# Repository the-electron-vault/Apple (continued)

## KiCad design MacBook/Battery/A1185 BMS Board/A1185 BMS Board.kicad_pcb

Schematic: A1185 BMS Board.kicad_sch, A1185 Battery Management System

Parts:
C1, C7, C13, C37: 100nF; MLCC-0603; Voltage 50V; Tolerance 10%; Manufacturer Part Number CL10B104KB8NNWC
C2, C3, C4, C8, C9, C14, C15, C19, C22, C28, C35: 100nF; MLCC-0402; Voltage 16V; Tolerance 10%; Manufacturer Part Number GCM155R71C104KA55J
C5: 4.7uF; MLCC-0805; Voltage 16V; Tolerance 10%; Manufacturer Part Number GRM21BR71C475KE51K
C6, C10, C21, C25, C33, C34: 1uF; MLCC-0805; Voltage 25V; Tolerance 10%; Manufacturer Part Number CL21B105KAFNNNE
C11, C12, C16, C17, C30, C32: 470nF; MLCC-0402; Voltage 10V; Tolerance 10%; Manufacturer Part Number KAM05AR71A474KH
C18, C27: 68pF; MLCC-0402; Voltage 50V; Tolerance 5%; Manufacturer Part Number CL05C680JB5NNNC
C20, C23, C24: 100nF; MLCC-0402; Voltage 16V; Tolerance 10%; Manufacturer Part Number GCM155R71C104KA55J; not fitted
C26: 150pF; MLCC-0402; Voltage 50V; Tolerance 5%; Manufacturer Part Number CL05C151JB5NNNC
C29: 47nF; MLCC-0603; Voltage 50V; Tolerance 10%; Manufacturer Part Number CL10B473KB8NNNC
C31: 2.2nF; MLCC-0402; Voltage 50V; Tolerance 10%; Manufacturer Part Number GRM155R71H222KA01D
C36: 1uF; MLCC-0805; Voltage 25V; Tolerance 10%; Manufacturer Part Number CL21B105KAFNNNE; not fitted
D1, D4, D5: 1SS355VMTE-17; SOD-323F; Voltage 90V; Manufacturer Part Number 1SS355VMTE-17
D2: RB751V-40TE-17; SOD-323F; Voltage 30V; Manufacturer Part Number RB751V-40TE-17
D3: UDZVTE-1733B; SOD-323F; Voltage 33V; Manufacturer Part Number UDZVTE-1733B
D6: UDZVTE-1718B; SOD-323F; Voltage 18V; Manufacturer Part Number UDZVTE-1718B
D7: MMBZ5V6ALT1G; SOT-23; Voltage 5.6V; Manufacturer Part Number MMBZ5V6ALT1G
F1: 12A; D6X; Voltage 32V; Manufacturer Part Number D6X
J1: BATT-TERM-POS; Manufacturer Part Number BATT-TERM-POS
J2, J3: CONN-1x1-0.6MM-TH; TH-0.6MM-1x1; Manufacturer Part Number CONN-1x1-0.6MM-TH
J4: BATT-TERM-NEG; Manufacturer Part Number BATT-TERM-NEG
J5: A1185 BLADE RCPT; A1185-BLADE-RECEPTACLE; Manufacturer Part Number A1185 BLADE RCPT
JP1: JUMPER-NO
LD1, LD2, LD3, LD4, LD5: HSMG-C110; HSMx-C110; Voltage 2.2V; Manufacturer Part Number HSMG-C110
Q1: AO3406; SOT-23; Voltage 30V; Manufacturer Part Number AO3406
Q2, Q3: TPC8107; SOIC-8; Voltage 30V; Manufacturer Part Number TPC8107
Q4, Q6: MMBT3906LT1G; SOT-23; Voltage 40V; Manufacturer Part Number MMBT3906LT1G
Q5, Q7, Q8, Q9, Q10: 2N7002K-T1-GE3; SOT-23; Voltage 60V; Manufacturer Part Number 2N7002K-T1-GE3
R1, R2, R3, R4, R14, R24, R28, R31, R32: 100; RES-0603; Tolerance 1%; Manufacturer Part Number RCA0603100RFKEA
R5, R11, R21, R36: 10; RES-0603; Tolerance 1%; Manufacturer Part Number RCA060310R0FKEA
R6, R7, R8, R34: 1k; RES-0402; Tolerance 1%; Manufacturer Part Number CRCW04021K00FKED
R9: 100k; RES-0603; Tolerance 1%; Manufacturer Part Number RCA0603100KFKEA
R10, R18, R35, R37: 100k; RES-0402; Tolerance 1%; Manufacturer Part Number CRCW0402100KFKED
R12, R19: 8.45k; RES-0402; Tolerance 1%; Manufacturer Part Number CRCW04028K45FKED
R13, R20, R33: 61.9k; RES-0402; Tolerance 1%; Manufacturer Part Number CRCW040261K9FKED
R15, R22, R23: 220k; RES-0402; Tolerance 1%; Manufacturer Part Number CRCW0402220KFKED
R16: 100; RES-0402; Tolerance 1%; Manufacturer Part Number CRCW0402100RFKED
R17: 100k; RES-0402; Tolerance 1%; Manufacturer Part Number CRCW0402100KFKED; not fitted
R25, R30, R38, R39, R40, R41, R43, R44, R45: 1M; RES-0402; Tolerance 1%; Manufacturer Part Number CRCW04021M00FKED
R26: 5m; RES-2512; Tolerance 1%; Manufacturer Part Number RLM25FEER005
R27, R29: 5.1k; RES-0402; Tolerance 1%; Manufacturer Part Number CRCW04025K10FKED
R42: 15k; RES-0402; Tolerance 1%; Manufacturer Part Number CRCW040215K0FKED
R46, R47: 100; RES-0805; Tolerance 1%; Manufacturer Part Number CRCW0805100RFKEA
R48: 130; RES-0402; Tolerance 1%; Manufacturer Part Number CRCW0402130RFKED
R49: 10k; RES-0402; Tolerance 1%; Manufacturer Part Number CRCW040210K0FKED
RT1, RT2: CONN-1x2-2MM-SMT; SMT-2MM-1x2; Manufacturer Part Number CONN-1x2-2MM-SMT
S1: APTCLGTV; Manufacturer Part Number APTCLGTV
TP1, TP2, TP3, TP4, TP5, TP6, TP7, TP8, TP9, TP10, TP11, TP12, TP13, TP14, TP15, TP16, TP17, TP18, TP19, TP20, TP21, TP22, TP23, TP24, TP25, TP26, TP27, TP28, TP29, TP30, TP31, TP32, TP33, TP34, TP35, TP36, TP37, TP38, TP39, TP40, TP41, TP42, TP43, TP44, TP45, TP46, TP47, TP48, TP49, TP50, TP51: TP; TP-SMT
U1: BQ29312ARTHR; VQFN-24-0.5-CH; Manufacturer Part Number BQ29312ARTHR
U2: BQ29401PW; TSSOP-8; Manufacturer Part Number BQ29401PW
U3: BQ20Z80DBT; TSSOP-38-0.5; Manufacturer Part Number BQ20Z80DBT

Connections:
/AFE_BAT: C6.1, D1.K, TP8.1, U1.22 (BAT)
/AFE_BAT_R: D1.A, R5.2
/AFE_CELL: R16.1, U1.8 (CELL)
/AFE_CHG: R29.2, U1.17 (CHG)
/AFE_DSG: R27.2, U1.23 (DSG)
/AFE_PACK: C10.1, D2.K, D3.K, TP13.1, U1.19 (PACK)
/AFE_PACK_R: D2.A, R11.2
/AFE_PMS: R9.2, TP12.1, U1.20 (PMS)
/AFE_SLEEP: R10.1, U1.16 (SLEEP)
/AFE_TOUT: R12.1, R19.1, TP17.1, U1.14 (TOUT)
/AFE_VC1_2: C1.1, R1.2, TP4.1, U1.1 (VC2), U1.24 (VC1)
/AFE_VC3: C2.1, R2.2, TP5.1, U1.2 (VC3)
/AFE_VC4: C3.1, R3.2, TP6.1, U1.3 (VC4)
/AFE_VC5: C4.1, R4.2, TP7.1, U1.4 (VC5)
/CAP_COM: C21.2, C25.1
/CHG_GATE: C29.2, Q3.G, R29.1, R30.2, TP33.1
/DSG_GATE: Q2.G, R25.2, R27.1, TP29.1
/FET_COM: Q2.D, Q3.D, TP31.1
/FUSE_TRIG: D4.K, Q1.1 (G), R15.2, R23.1, TP19.1
/FUSE_TRIG_JP: F1.3 (TRIG), JP1.2
/FUSE_TRIG_L: D5.K, JP1.1, Q1.3 (D), TP23.1
/GAUGE_DISP_L: R34.1, U3.17 (~DISP)
/GAUGE_FILT: C26.1, R33.1, U3.32 (FILT)
/GAUGE_FILT_RC: C31.1, R33.2
/GAUGE_LED1: Q5.1 (G), R38.2, TP40.1, U3.24 (LED1)
/GAUGE_LED2: Q7.1 (G), R39.2, TP42.1, U3.23 (LED2)
/GAUGE_LED3: Q8.1 (G), R40.2, U3.22 (LED3)
/GAUGE_LED4: Q9.1 (G), R43.2, TP46.1, U3.21 (LED4)
/GAUGE_LED5: Q10.1 (G), R45.2, TP47.1, U3.20 (LED5)
/GAUGE_MRST: C14.2, R17.2, R18.1, U3.26 (MRST)
/GAUGE_PFIN_L: D5.A, R22.2, U3.18 (~PFIN)
/GAUGE_RBI: C32.1, U3.9 (RBI)
/GAUGE_SAFE: D4.A, U3.7 (SAFE)
/GAUGE_SCL: R31.1, U3.15 (SMBC)
/GAUGE_SDA: R32.1, U3.16 (SMBD)
/GAUGE_SR1: C19.2, C22.1, R24.1, TP27.1, U3.28 (SR1)
/GAUGE_SR2: C22.2, C28.2, R28.1, TP30.1, U3.27 (SR2)
/GAUGE_TS1: C11.1, R12.2, R13.1, RT2.1, TP14.1, U3.2 (TS1)
/GAUGE_TS2: C16.1, R19.2, R20.1, RT1.1, TP20.1, U3.3 (TS2)
/GAUGE_VDDA: C27.1, C30.1, R36.2, TP34.1, U3.31 (VDDA)
/GAUGE_VIN: C15.1, R16.2, TP18.1, U3.1 (VIN)
/GAUGE_XCK2: R35.1, U3.33 (XCK2/ROSC)
/LED1: LD1.K, LD2.A, Q5.3 (D), TP48.1
/LED2: LD2.K, LD3.A, Q7.3 (D), TP49.1
/LED3: LD3.K, LD4.A, Q8.3 (D), TP50.1
/LED4: LD4.K, LD5.A, Q9.3 (D), TP51.1
/LED5: LD5.K, Q10.3 (D)
/LED_I_SRC: D6.K, LD1.A, Q6.3 (C), R42.2, TP39.1
/LED_I_SRC_B: Q4.3 (C), Q6.1 (B), R42.1, TP38.1
/LED_I_SRC_FB: Q4.1 (B), Q6.2 (E), R48.2, TP41.1
/NC_ALERT: J5.2
/NTC: C37.1, J5.5, R49.1, TP45.1
/PACK_P_CAP: C33.2, C34.1
/PP_3V3_GAUGE: C17.1, C18.1, R21.2, TP21.1, U3.8 (VDDD)
/PP_10V8_VP_FUSE: F1.1 (FUSE1), Q2.S, R25.1, TP28.1
/PROT_CD: C12.1, U2.6 (CD)
/PROT_OUT: R15.1, TP16.1, U2.8 (OUT)
/PROT_VC1_2: C7.1, R6.2, U2.1 (VC1), U2.2 (VC2)
/PROT_VC3: C7.2, C8.1, R7.2, TP10.1, U2.3 (VC3)
/PROT_VC4: C8.2, C9.1, R8.2, TP11.1, U2.5 (VC4)
/PROT_VDD: C13.1, R14.2, TP15.1, U2.7 (VDD)
/SCLK: TP24.1, U1.10 (SCLK), U3.6 (SCLK)
/SDATA: TP22.1, U1.11 (SDATA), U3.10 (SDATA)
/SMB_SCL: D7.1 (K1), R31.2, R41.1, R46.1, TP35.1
/SMB_SCL_CONN: J5.3, R46.2
/SMB_SDA: D7.2 (K2), R32.2, R44.1, R47.1, TP36.1
/SMB_SDA_CONN: J5.4, R47.2
/SOC_SW: C35.1, R34.2, R37.2, S1.2, TP37.1
/VH: J2.1, R2.1, R7.1, TP2.1
/VL: J3.1, R3.1, R8.1, TP3.1
/WDI_CLKOUT: TP25.1, U1.7 (WDI), U3.35 (CLKOUT)
/XALERT: U1.13 (XALERT), U3.25 (XALERT)
GND: C1.2, C2.2, C3.2, C4.2, C5.2, C6.2, C10.2, C11.2, C15.2, C16.2, C17.2, C18.2, C19.1, C20.2, C23.2, C24.1, C24.2, C26.2, C27.2, C28.1, C30.2, C31.2, C32.2, C34.2, C35.2, C36.2, C37.2, D3.A, D6.A, D7.3 (A), J5.6, Q5.2 (S), Q7.2 (S), Q8.2 (S), Q9.2 (S), Q10.2 (S), R10.2, R13.2, R18.2, R20.2, R26.2, R28.2, R35.2, R41.2, R44.2, R49.2, RT1.2, RT2.2, S1.1, TP32.1, TP43.1, U1.6 (SR2), U1.9 (GND), U1.12 (GND), U1.EP (GND), U3.5 (~PRES), U3.11 (VSSD), U3.19 (VSSD), U3.29 (VSSA), U3.30 (VSSA), U3.34 (XCK1/VSSA), U3.38 (VSSD)
PP_3V3_AFE_REG: C5.1, C14.1, R17.1, R21.1, R22.1, R36.1, R37.1, R38.1, R39.1, R40.1, R43.1, R45.1, TP9.1, U1.15 (REG)
PP_10V8_PACK_P: C25.2, C29.1, C33.1, C36.1, J5.1, Q3.S, R9.1, R11.1, R30.1, TP44.1
PP_10V8_VP: C21.1, F1.2 (FUSE2), J1.1, Q4.2 (E), R1.1, R5.1, R6.1, R14.1, R48.1, TP1.1
VG: C9.2, C12.2, C13.2, C20.1, C23.1, J4.1, Q1.2 (S), R4.1, R23.2, R24.2, R26.1, TP26.1, U1.5 (SR1), U2.4 (GND)

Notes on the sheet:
DESIGN NOTE: PMS = PACK -> CHG = ON PMS = GND -> CHG = OFF
DESIGN NOTE: Pin 2 is an active-low alert signal to the system. Not connected on BMS side.
DESIGN NOTE: R48 is likely a 10k NTC provision (unused). This pin is not connected on the system-side battery transfer board.
DESIGN NOTE: I_LED = 0.7V/${6753d329-0cbb-4c78-95cb-1bccc96fa04a:VALUE} = 5.38mA
DESIGN NOTE: t_d = 1.2V * ${da373f2d-cdde-46c7-ad6d-827585d9abf0:VALUE}/0.2uA = 2.82s

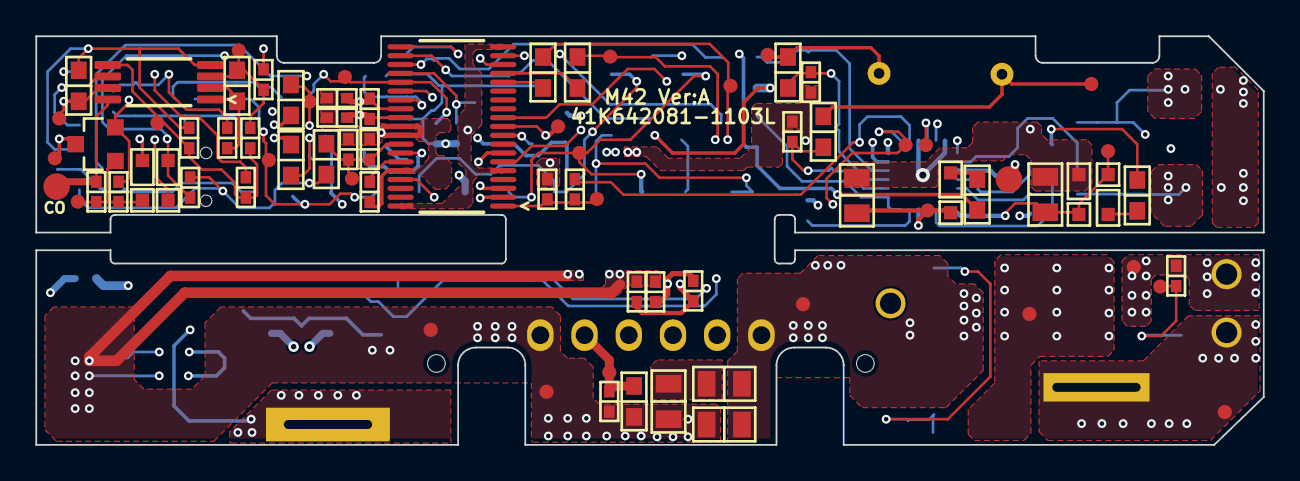
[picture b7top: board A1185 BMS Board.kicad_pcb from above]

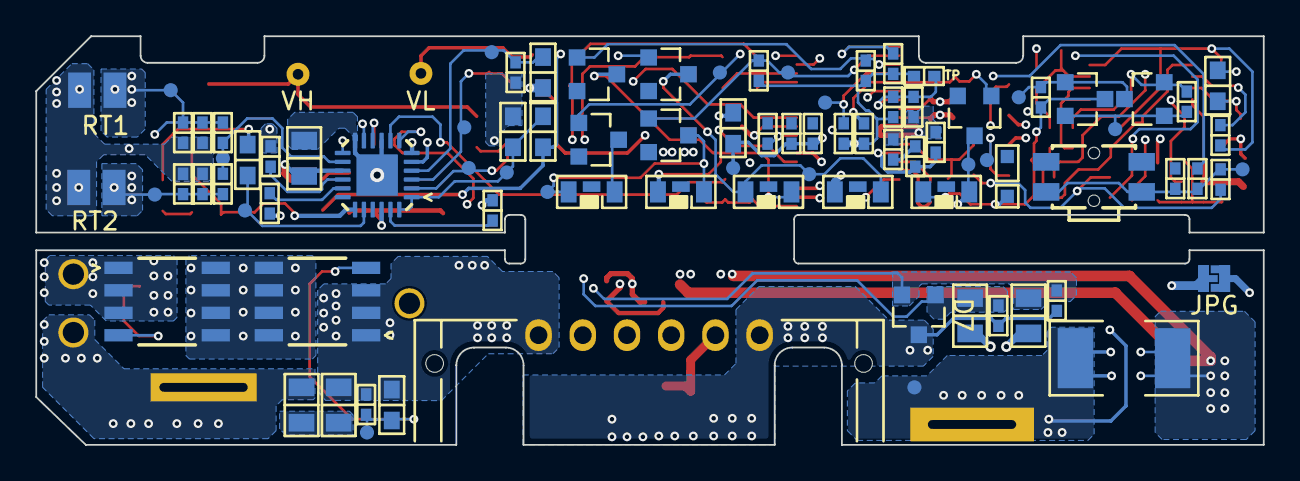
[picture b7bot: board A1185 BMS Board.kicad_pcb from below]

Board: 4 copper layers, 69.4 x 23.1 mm, 172 parts (92 on the bottom side), 76 nets.

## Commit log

2025-04-19 Initial commit for iPod Video.
2025-10-25 Added A1185 BMS Board
2025-11-04 Added design files for 820-3503
2025-11-10 Added design files for 821-0828
2026-01-06 Added design files for Cinema Display barrel jack adapter board.
2026-01-06 Added copyright information.
2026-01-27 Added files for iPod 4th Generation
    - 632-0259: HDD Flex Cable
    - 820-1635: Headphone/Hold Switch Board
    - STEP model for Dock Connector Bezel
    - COTS 1.8" IDE to CF Adapter Board
    - TEV-AAPL-FPC-00001: CompactFlash cable for 4th Generation iPod
    - TEV-AAPL-IPOD-4-CASE-00001: Case for 4th Generation iPod with Thick Back Plate
